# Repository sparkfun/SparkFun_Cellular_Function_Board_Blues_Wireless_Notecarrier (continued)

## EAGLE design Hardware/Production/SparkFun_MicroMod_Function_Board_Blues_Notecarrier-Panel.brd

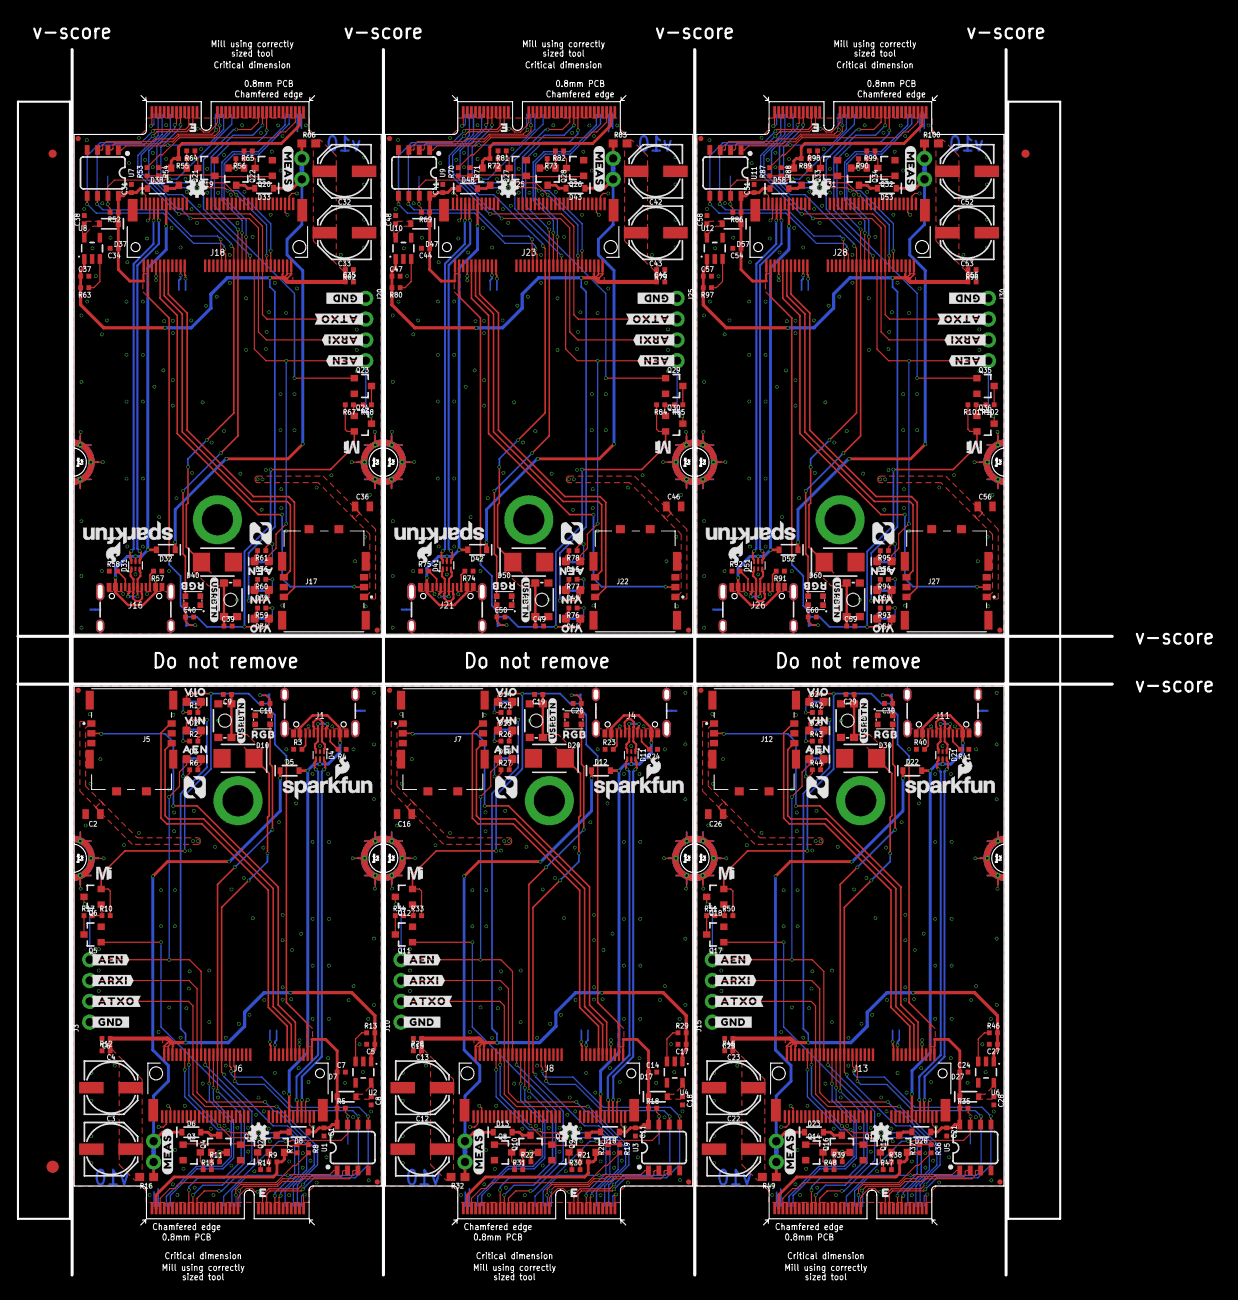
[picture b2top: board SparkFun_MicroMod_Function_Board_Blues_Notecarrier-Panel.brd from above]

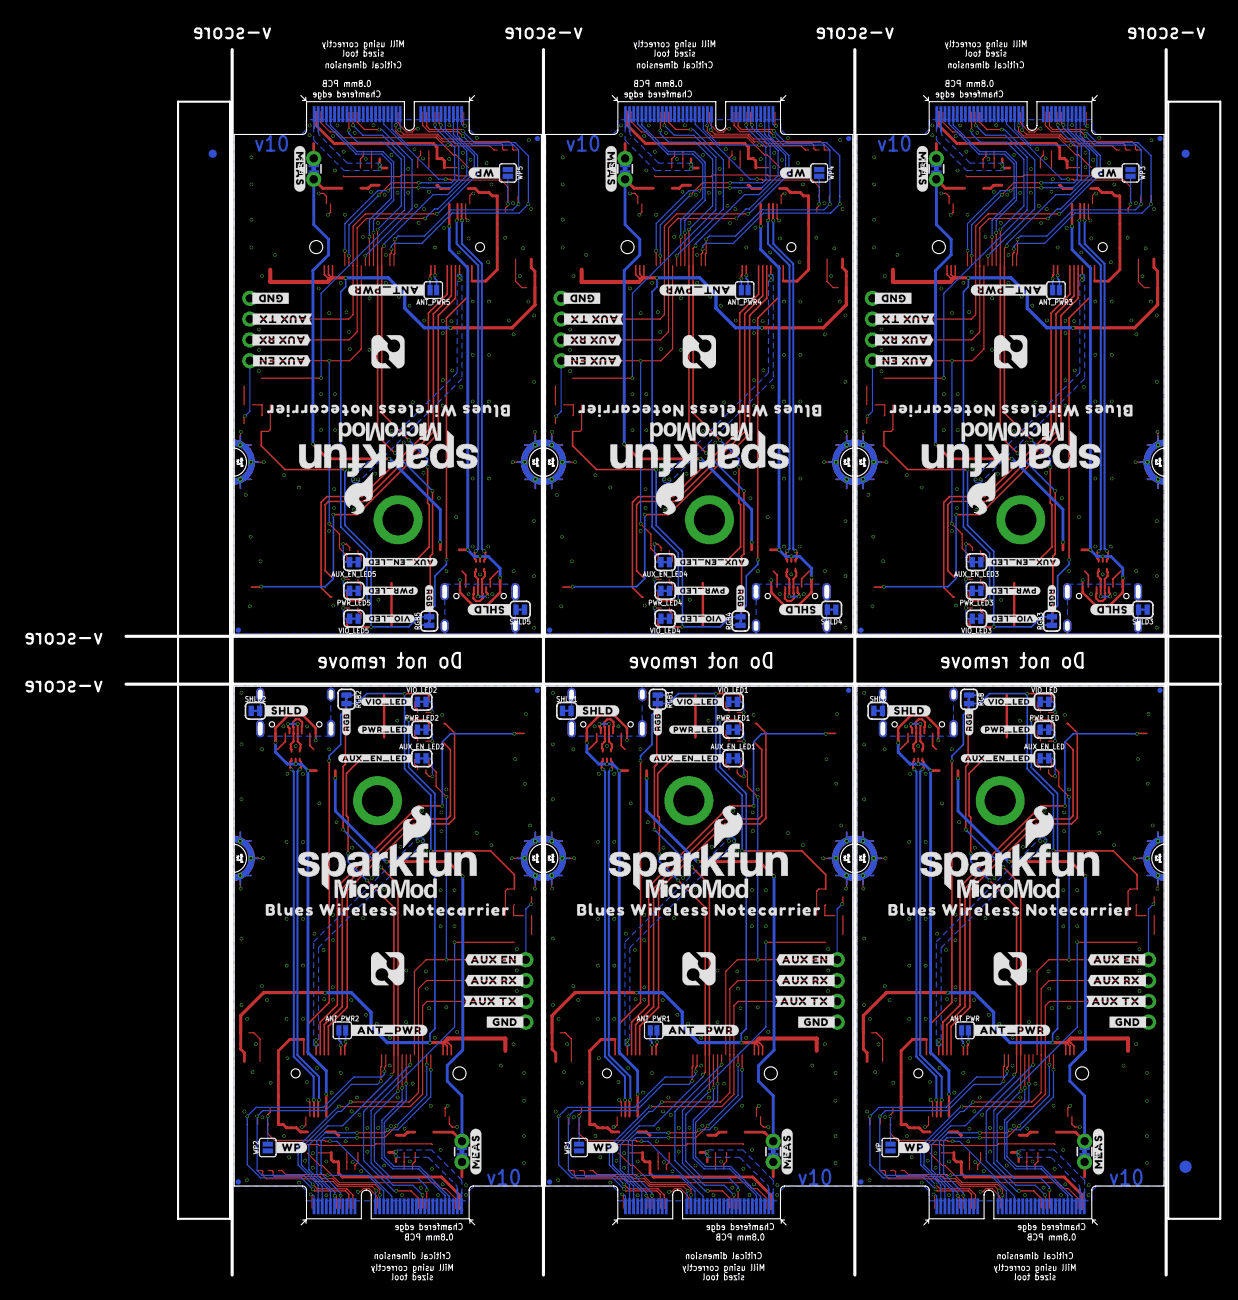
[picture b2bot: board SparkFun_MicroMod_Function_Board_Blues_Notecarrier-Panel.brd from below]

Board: 2 copper layers, 133.6 x 149.6 mm, 576 parts (159 on the bottom side), 342 nets.

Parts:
ANT_PWR, ANT_PWR1, ANT_PWR2, ANT_PWR3, ANT_PWR4, ANT_PWR5: JUMPER-SMT_2_NO_SILK; SMT-JUMPER_2_NO_SILK
AUX_EN_LED, AUX_EN_LED1, AUX_EN_LED2, AUX_EN_LED3, AUX_EN_LED4, AUX_EN_LED5: JUMPER-SMT_2_NC_TRACE_SILK; SMT-JUMPER_2_NC_TRACE_SILK
C1, C5, C6, C7, C10, C11, C14, C15, C17, C20, C21, C24, C25, C27, C30, C31, C34, C35, C37, C40, C41, C44, C45, C47, C50, C51, C54, C55, C57, C60: 0.1uF; 0402-TIGHT
C2, C16, C26, C36, C46, C56: 10uF; 0805
C3, C4, C12, C13, C22, C23, C32, C33, C42, C43, C52, C53: 100uF; PANASONIC_D
C8, C9, C18, C19, C28, C29, C38, C39, C48, C49, C58, C59: 1.0uF; 0402-TIGHT
D1, D2, D14, D15, D24, D25, D34, D35, D44, D45, D54, D55: RED; LED-0603
D3, D16, D26, D36, D46, D56: BLUE; LED-0603
D4, D11, D21, D31, D41, D51: PRTR5V0U2F; SOT886
D5, D6, D12, D13, D22, D23, D32, D33, D42, D43, D52, D53: 3A/10V/280mV; SOD-323
D7, D8, D17, D18, D27, D28, D37, D38, D47, D48, D57, D58: 0.5A/40V/420mV; SOD-323
D9, D19, D29, D39, D49, D59: SMBJP6KE6.8A-TP; DO-214AA
D10, D20, D30, D40, D50, D60: WS2812_2020; WS2812-2020
E$1, E$2, E$3, E$4: FIDUCIAL-1X2
E$5, E$6: FIDUCIAL-1.5X3
FD1, FD2, FD3, FD4, FD5, FD6, FD7, FD8, FD9, FD10, FD11, FD12, FD13, FD14, FD15, FD16, FD17, FD18, FD19, FD20, FD21, FD22, FD23, FD24: FIDUCIALUFIDUCIAL; FIDUCIAL-MICRO
H1, H2, H3, H4, H5, H6: STAND-OFF-REFLOW-M2.5_2.5MM_TALL; STAND-OFF-REFLOW-M2.5
J1, J4, J11, J16, J21, J26: USB-C-16P-2LAYER-PADS
J2, J9, J14, J19, J24, J29: MICROMOD_FUNCTION_STANDARD; M.2-CARD-E-22_FUNCTION_STANDARD
J3, J10, J15, J20, J25, J30: 1X04_NO_SILK
J5, J7, J12, J17, J22, J27: NANO_SIM_MOLEX_104224-0820
J6, J8, J13, J18, J23, J28: NOTECARD; M.2-CONNECTOR-E
LOGO1, LOGO4, LOGO6, LOGO8, LOGO10, LOGO12: SFE_LOGO_NAME_FLAME.1_INCH; SFE_LOGO_NAME_FLAME_.1
LOGO2, LOGO3, LOGO5, LOGO7, LOGO9, LOGO11: OSHW-LOGOMINI; OSHW-LOGO-MINI
MEAS, MEAS1, MEAS2, MEAS3, MEAS4, MEAS5: JUMPER-COMBO_2_NC_TRACE; COMBO-JUMPER_2_NC_TRACE
PWR_LED, PWR_LED1, PWR_LED2, PWR_LED3, PWR_LED4, PWR_LED5: JUMPER-SMT_2_NC_TRACE_SILK; SMT-JUMPER_2_NC_TRACE_SILK
Q1, Q3, Q5, Q7, Q8, Q11, Q13, Q14, Q17, Q19, Q20, Q23, Q25, Q26, Q29, Q31, Q32, Q35: 220mA/50V/3.5Ω; SOT23-3
Q2, Q4, Q6, Q9, Q10, Q12, Q15, Q16, Q18, Q21, Q22, Q24, Q27, Q28, Q30, Q33, Q34, Q36: 20V/4.2A/52mΩ/1.4W; SOT23-3
R1, R2, R25, R26, R42, R43, R59, R60, R76, R77, R93, R94: 1k; 0402-TIGHT
R3, R4, R23, R24, R40, R41, R57, R58, R74, R75, R91, R92: 5.1k; 0402-TIGHT
R5, R7, R9, R10, R11, R13, R18, R20, R21, R22, R29, R33, R35, R37, R38, R39, R46, R50, R52, R54, R55, R56, R63, R67, R69, R71, R72, R73, R80, R84, R86, R88, R89, R90, R97, R101: 10k; 0402-TIGHT
R6, R27, R44, R61, R78, R95: 2.2k; 0402-TIGHT
R8, R19, R36, R53, R70, R87: 560Ω; 0402-TIGHT
R12, R28, R45, R62, R79, R96: 2.2M; 0402-TIGHT
R14, R15, R17, R30, R31, R34, R47, R48, R51, R64, R65, R68, R81, R82, R85, R98, R99, R102: 100; 0402-TIGHT
R16, R32, R49, R66, R83, R100: 1; 0603
RGB, RGB1, RGB2, RGB3, RGB4, RGB5: JUMPER-SMT_2_NC_TRACE_SILK; SMT-JUMPER_2_NC_TRACE_SILK
S1, S2, S3, S4, S5, S6: MOMENTARY-SWITCH-SPST-SMD-4.6X2.8MM; TACTILE_SWITCH_SMD_4.6X2.8MM
SHLD, SHLD1, SHLD2, SHLD3, SHLD4, SHLD5: JUMPER-SMT_2_NC_TRACE_SILK; SMT-JUMPER_2_NC_TRACE_SILK
U1, U3, U5, U7, U9, U11: EEPROM; SO08
U2, U4, U6, U8, U10, U12: TCR2EF33; SOT23-5
U$1, U$27, U$59, U$88, U$117, U$146: AEN1
U$2, U$28, U$60, U$89, U$118, U$147: VIN3
U$3, U$32, U$61, U$90, U$119, U$148: VIO4
U$4, U$42, U$71, U$100, U$129, U$158: #VIO_LED_#21
U$5, U$53, U$82, U$111, U$140, U$169: #_ARXI#0
U$6, U$33, U$62, U$91, U$120, U$149: SFE_LOGO_FLAME_STOP_.1
U$7, U$34, U$63, U$92, U$121, U$150: #_GND_#0
U$8, U$36, U$65, U$94, U$123, U$152: #_WP#2
U$9, U$49, U$78, U$107, U$136, U$165: BLUES_WIRELESS_NOTECARRIER0
U$10, U$50, U$79, U$108, U$137, U$166: NOTEHUB_BLUES#SVG7
U$11, U$54, U$83, U$112, U$141, U$170: #_ATXO#0
U$12, U$51, U$80, U$109, U$138, U$167: #AUX_TX_#0
U$13, U$55, U$84, U$113, U$142, U$171: #_AEN#0
U$14, U$35, U$64, U$93, U$122, U$151: SFE_LOGO_NAME_FLAME_.2
U$15, U$52, U$81, U$110, U$139, U$168: #AUX_RX_#0
U$16, U$17, U$37, U$38, U$66, U$67, U$95, U$96, U$124, U$125, U$153, U$154: #MEAS#4
U$18, U$39, U$68, U$97, U$126, U$155: #_ANT_PWR#5
U$19, U$41, U$70, U$99, U$128, U$157: #AUX_EN_LED_#20
U$20, U$43, U$72, U$101, U$130, U$159: #_SHLD#23
U$21, U$40, U$69, U$98, U$127, U$156: #PWR_LED_#17
U$22, U$44, U$73, U$102, U$131, U$160: #_GND_#24
U$23, U$47, U$76, U$105, U$134, U$163: NOTEHUB_BLUES#SVG5
U$24, U$56, U$85, U$114, U$143, U$172: #RGB_#0
U$25, U$57, U$86, U$115, U$144, U$173: #USRBTN#0
U$26, U$58, U$87, U$116, U$145, U$174: RGB0
U$29, U$45, U$74, U$103, U$132, U$161: MICROMOD_MI_LOGO_.35
U$30, U$46, U$75, U$104, U$133, U$162: #AUX_EN_#0
U$31, U$48, U$77, U$106, U$135, U$164: MICROMOD_LOGO_.5
VIO_LED, VIO_LED1, VIO_LED2, VIO_LED3, VIO_LED4, VIO_LED5: JUMPER-SMT_2_NC_TRACE_SILK; SMT-JUMPER_2_NC_TRACE_SILK
WP, WP1, WP2, WP3, WP4, WP5: JUMPER-SMT_2_NO_SILK; SMT-JUMPER_2_NO_SILK

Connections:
3.3V: C1.1, C7.1, D1.A, D7.C, D8.C, J6.2, J6.4, Q6.2, R5.1, R10.2, RGB.2, U1.8
3.3V1: C11.1, C14.1, D14.A, D17.C, D18.C, J8.2, J8.4, Q12.2, R18.1, R33.2, RGB1.2, U3.8
3.3V2: C21.1, C24.1, D24.A, D27.C, D28.C, J13.2, J13.4, Q18.2, R35.1, R50.2, RGB2.2, U5.8
3.3V3: C31.1, C34.1, D34.A, D37.C, D38.C, J18.2, J18.4, Q24.2, R52.1, R67.2, RGB3.2, U7.8
3.3V4: C41.1, C44.1, D44.A, D47.C, D48.C, J23.2, J23.4, Q30.2, R69.1, R84.2, RGB4.2, U9.8
3.3V5: C51.1, C54.1, D54.A, D57.C, D58.C, J28.2, J28.4, Q36.2, R86.1, R101.2, RGB5.2, U11.8
3V3_IN: J2.73, Q2.2, R7.1, R9.2
3V3_IN1: J9.73, Q9.2, R20.1, R21.2
3V3_IN2: J14.73, Q15.2, R37.1, R38.2
3V3_IN3: J19.73, Q21.2, R54.1, R55.2
3V3_IN4: J24.73, Q27.2, R71.1, R72.2
3V3_IN5: J29.73, Q33.2, R88.1, R89.2
A0: J2.36, U1.1
A1: J2.34, U1.2
A2: J2.32, U1.3
A3: J9.36, U3.1
A4: J9.32, U3.3
A5: J9.34, U3.2
A6: J14.36, U5.1
A7: J14.32, U5.3
A8: J14.34, U5.2
A9: J19.36, U7.1
A10: J19.32, U7.3
A11: J19.34, U7.2
A12: J24.36, U9.1
A13: J24.32, U9.3
A14: J24.34, U9.2
A15: J29.36, U11.1
A16: J29.32, U11.3
A17: J29.34, U11.2
ATTN: J2.53, J6.54
ATTN1: J8.54, J9.53
ATTN2: J13.54, J14.53
ATTN3: J18.54, J19.53
ATTN4: J23.54, J24.53
ATTN5: J28.54, J29.53
AUX1/DFU_!ACTIVE!/USR_BTN: C9.1, D9.C, J2.10, J6.46, S1.3, S1.4
AUX1/DFU_!ACTIVE!/USR_BTN1: C19.1, D19.C, J8.46, J9.10, S2.3, S2.4
AUX1/DFU_!ACTIVE!/USR_BTN2: C29.1, D29.C, J13.46, J14.10, S3.3, S3.4
AUX1/DFU_!ACTIVE!/USR_BTN3: C39.1, D39.C, J18.46, J19.10, S4.3, S4.4
AUX1/DFU_!ACTIVE!/USR_BTN4: C49.1, D49.C, J23.46, J24.10, S5.3, S5.4
AUX1/DFU_!ACTIVE!/USR_BTN5: C59.1, D59.C, J28.46, J29.10, S6.3, S6.4
AUX2/RGB: D10.DI, J2.57, J6.48
AUX2/RGB1: D20.DI, J8.48, J9.57
AUX2/RGB2: D30.DI, J13.48, J14.57
AUX2/RGB3: D40.DI, J18.48, J19.57
AUX2/RGB4: D50.DI, J23.48, J24.57
AUX2/RGB5: D60.DI, J28.48, J29.57
AUX3/DFU_!BOOT!: J2.66, J6.50
AUX3/DFU_!BOOT!1: J8.50, J9.66
AUX3/DFU_!BOOT!2: J13.50, J14.66
AUX3/DFU_!BOOT!3: J18.50, J19.66
AUX3/DFU_!BOOT!4: J23.50, J24.66
AUX3/DFU_!BOOT!5: J28.50, J29.66
AUX4/DFU_!RST!: J2.68, J6.52
AUX4/DFU_!RST!1: J8.52, J9.68
AUX4/DFU_!RST!2: J13.52, J14.68
AUX4/DFU_!RST!3: J18.52, J19.68
AUX4/DFU_!RST!4: J23.52, J24.68
AUX4/DFU_!RST!5: J28.52, J29.68
AUX_EN: D3.A, J3.4, J6.56, Q6.3
AUX_EN1: D16.A, J8.56, J10.4, Q12.3
AUX_EN2: D26.A, J13.56, J15.4, Q18.3
AUX_EN3: D36.A, J18.56, J20.4, Q24.3
AUX_EN4: D46.A, J23.56, J25.4, Q30.3
AUX_EN5: D56.A, J28.56, J30.4, Q36.3
AUX_PWR: J2.55, Q5.1
AUX_PWR1: J9.55, Q11.1
AUX_PWR2: J14.55, Q17.1
AUX_PWR3: J19.55, Q23.1
AUX_PWR4: J24.55, Q29.1
AUX_PWR5: J29.55, Q35.1
AUX_RX/MCU_TX: J2.6, J3.3, J6.58
AUX_RX/MCU_TX1: J8.58, J9.6, J10.3
AUX_RX/MCU_TX2: J13.58, J14.6, J15.3
AUX_RX/MCU_TX3: J18.58, J19.6, J20.3
AUX_RX/MCU_TX4: J23.58, J24.6, J25.3
AUX_RX/MCU_TX5: J28.58, J29.6, J30.3
AUX_TX/MCU_RX: J2.4, J3.2, J6.60
AUX_TX/MCU_RX1: J8.60, J9.4, J10.2
AUX_TX/MCU_RX2: J13.60, J14.4, J15.2
AUX_TX/MCU_RX3: J18.60, J19.4, J20.2
AUX_TX/MCU_RX4: J23.60, J24.4, J25.2
AUX_TX/MCU_RX5: J28.60, J29.4, J30.2
EWP: J2.40, R5.2, U1.7, WP.2
EWP1: J9.40, R18.2, U3.7, WP1.2
EWP2: J14.40, R35.2, U5.7, WP2.2
EWP3: J19.40, R52.2, U7.7, WP3.2
EWP4: J24.40, R69.2, U9.7, WP4.2
EWP5: J29.40, R86.2, U11.7, WP5.2
GND: AUX_EN_LED.1, C1.2, C2.2, C3.-, C4.-, C5.2, C6.2, C7.2, C8.2, C9.2, C10.2, D4.2, D9.A, D10.GND, H1.1, J1.GND, J1.GND2, J2.1, J2.2, J2.8, J2.33, J2.39, J2.45, J2.75, J2.GND1, J2.GND2, J2.GND3, J2.GND4, J2.GND5, J2.GND6, J3.1, J5.G1, J5.G2, J5.G3, J5.G4, J5.S4, J6.3, J6.5, J6.6, J6.11, J6.18, J6.33, J6.39, J6.45, J6.51, J6.57, J6.71, J6.73, PWR_LED.1, Q1.2, Q3.2, Q5.2, R3.1, R4.1, R12.1, S1.1, S1.2, SHLD.1, U1.4, U2.2, VIO_LED.1, WP.1
GND1: AUX_EN_LED1.1, C11.2, C12.-, C13.-, C14.2, C15.2, C16.2, C17.2, C18.2, C19.2, C20.2, D11.2, D19.A, D20.GND, H2.1, J4.GND, J4.GND2, J7.G1, J7.G2, J7.G3, J7.G4, J7.S4, J8.3, J8.5, J8.6, J8.11, J8.18, J8.33, J8.39, J8.45, J8.51, J8.57, J8.71, J8.73, J9.1, J9.2, J9.8, J9.33, J9.39, J9.45, J9.75, J9.GND1, J9.GND2, J9.GND3, J9.GND4, J9.GND5, J9.GND6, J10.1, PWR_LED1.1, Q7.2, Q8.2, Q11.2, R23.1, R24.1, R28.1, S2.1, S2.2, SHLD1.1, U3.4, U4.2, VIO_LED1.1, WP1.1
GND2: AUX_EN_LED2.1, C21.2, C22.-, C23.-, C24.2, C25.2, C26.2, C27.2, C28.2, C29.2, C30.2, D21.2, D29.A, D30.GND, H3.1, J11.GND, J11.GND2, J12.G1, J12.G2, J12.G3, J12.G4, J12.S4, J13.3, J13.5, J13.6, J13.11, J13.18, J13.33, J13.39, J13.45, J13.51, J13.57, J13.71, J13.73, J14.1, J14.2, J14.8, J14.33, J14.39, J14.45, J14.75, J14.GND1, J14.GND2, J14.GND3, J14.GND4, J14.GND5, J14.GND6, J15.1, PWR_LED2.1, Q13.2, Q14.2, Q17.2, R40.1, R41.1, R45.1, S3.1, S3.2, SHLD2.1, U5.4, U6.2, VIO_LED2.1, WP2.1
GND3: AUX_EN_LED3.1, C31.2, C32.-, C33.-, C34.2, C35.2, C36.2, C37.2, C38.2, C39.2, C40.2, D31.2, D39.A, D40.GND, H4.1, J16.GND, J16.GND2, J17.G1, J17.G2, J17.G3, J17.G4, J17.S4, J18.3, J18.5, J18.6, J18.11, J18.18, J18.33, J18.39, J18.45, J18.51, J18.57, J18.71, J18.73, J19.1, J19.2, J19.8, J19.33, J19.39, J19.45, J19.75, J19.GND1, J19.GND2, J19.GND3, J19.GND4, J19.GND5, J19.GND6, J20.1, PWR_LED3.1, Q19.2, Q20.2, Q23.2, R57.1, R58.1, R62.1, S4.1, S4.2, SHLD3.1, U7.4, U8.2, VIO_LED3.1, WP3.1
GND4: AUX_EN_LED4.1, C41.2, C42.-, C43.-, C44.2, C45.2, C46.2, C47.2, C48.2, C49.2, C50.2, D41.2, D49.A, D50.GND, H5.1, J21.GND, J21.GND2, J22.G1, J22.G2, J22.G3, J22.G4, J22.S4, J23.3, J23.5, J23.6, J23.11, J23.18, J23.33, J23.39, J23.45, J23.51, J23.57, J23.71, J23.73, J24.1, J24.2, J24.8, J24.33, J24.39, J24.45, J24.75, J24.GND1, J24.GND2, J24.GND3, J24.GND4, J24.GND5, J24.GND6, J25.1, PWR_LED4.1, Q25.2, Q26.2, Q29.2, R74.1, R75.1, R79.1, S5.1, S5.2, SHLD4.1, U9.4, U10.2, VIO_LED4.1, WP4.1
GND5: AUX_EN_LED5.1, C51.2, C52.-, C53.-, C54.2, C55.2, C56.2, C57.2, C58.2, C59.2, C60.2, D51.2, D59.A, D60.GND, H6.1, J26.GND, J26.GND2, J27.G1, J27.G2, J27.G3, J27.G4, J27.S4, J28.3, J28.5, J28.6, J28.11, J28.18, J28.33, J28.39, J28.45, J28.51, J28.57, J28.71, J28.73, J29.1, J29.2, J29.8, J29.33, J29.39, J29.45, J29.75, J29.GND1, J29.GND2, J29.GND3, J29.GND4, J29.GND5, J29.GND6, J30.1, PWR_LED5.1, Q31.2, Q32.2, Q35.2, R91.1, R92.1, R96.1, S6.1, S6.2, SHLD5.1, U11.4, U12.2, VIO_LED5.1, WP5.1
unnamed: J2.71, R8.2
unnamed: Q2.1, R9.1, R14.2
unnamed: Q4.1, R11.1, R15.2
unnamed: D1.C, R1.2
unnamed: R13.1, U2.3
unnamed: D2.C, R2.2
unnamed: D8.A, Q2.3
unnamed: J1.B5, R3.2
unnamed: J1.A5, R4.2
unnamed: C8.1, D7.A, U2.5
unnamed: PWR_LED.2, R2.1
unnamed: R1.1, VIO_LED.2
unnamed: D3.C, R6.2
unnamed: AUX_EN_LED.2, R6.1
unnamed: Q1.3, R14.1
unnamed: Q3.3, R15.1
unnamed: MEAS.2, MEAS.4, R16.1
unnamed: C10.1, D10.VCC, RGB.1
unnamed: Q6.1, R10.1, R17.2
unnamed: Q5.3, R17.1
unnamed: J9.71, R19.2
unnamed: Q9.1, R21.1, R30.2
unnamed: Q10.1, R22.1, R31.2
unnamed: J4.B5, R23.2
unnamed: J4.A5, R24.2
unnamed: D12.C, D13.C, MEAS1.1, MEAS1.3
unnamed: D14.C, R25.2
unnamed: D15.C, R26.2
unnamed: PWR_LED1.2, R26.1
unnamed: R25.1, VIO_LED1.2
unnamed: D16.C, R27.2
unnamed: AUX_EN_LED1.2, R27.1
unnamed: R29.1, U4.3
unnamed: C18.1, D17.A, U4.5
unnamed: D18.A, Q9.3
unnamed: Q7.3, R30.1
unnamed: D5.C, D6.C, MEAS.1, MEAS.3
unnamed: Q8.3, R31.1
unnamed: MEAS1.2, MEAS1.4, R32.1
unnamed: C20.1, D20.VCC, RGB1.1
unnamed: Q12.1, R33.1, R34.2
unnamed: Q11.3, R34.1
unnamed: J14.71, R36.2
unnamed: Q15.1, R38.1, R47.2
unnamed: Q16.1, R39.1, R48.2
unnamed: J11.B5, R40.2
unnamed: J11.A5, R41.2
unnamed: D22.C, D23.C, MEAS2.1, MEAS2.3
unnamed: D24.C, R42.2
unnamed: D25.C, R43.2
unnamed: PWR_LED2.2, R43.1
unnamed: R42.1, VIO_LED2.2
unnamed: D26.C, R44.2
unnamed: AUX_EN_LED2.2, R44.1
unnamed: R46.1, U6.3
unnamed: C28.1, D27.A, U6.5
unnamed: D28.A, Q15.3
unnamed: Q13.3, R47.1
unnamed: Q14.3, R48.1
unnamed: MEAS2.2, MEAS2.4, R49.1
unnamed: C30.1, D30.VCC, RGB2.1
unnamed: Q18.1, R50.1, R51.2
unnamed: Q17.3, R51.1
unnamed: J19.71, R53.2
unnamed: Q21.1, R55.1, R64.2
unnamed: Q22.1, R56.1, R65.2
unnamed: J16.B5, R57.2
unnamed: J16.A5, R58.2
unnamed: D32.C, D33.C, MEAS3.1, MEAS3.3
unnamed: D34.C, R59.2
unnamed: D35.C, R60.2
unnamed: PWR_LED3.2, R60.1
unnamed: R59.1, VIO_LED3.2
unnamed: D36.C, R61.2
unnamed: AUX_EN_LED3.2, R61.1
unnamed: R63.1, U8.3
unnamed: C38.1, D37.A, U8.5
unnamed: D38.A, Q21.3
unnamed: Q19.3, R64.1
unnamed: Q20.3, R65.1
unnamed: MEAS3.2, MEAS3.4, R66.1
unnamed: C40.1, D40.VCC, RGB3.1
unnamed: Q24.1, R67.1, R68.2
unnamed: Q23.3, R68.1
unnamed: J24.71, R70.2
unnamed: Q27.1, R72.1, R81.2
unnamed: Q28.1, R73.1, R82.2
unnamed: J21.B5, R74.2
unnamed: J21.A5, R75.2
unnamed: D42.C, D43.C, MEAS4.1, MEAS4.3
unnamed: D44.C, R76.2
unnamed: D45.C, R77.2
unnamed: PWR_LED4.2, R77.1
unnamed: R76.1, VIO_LED4.2
unnamed: D46.C, R78.2
unnamed: AUX_EN_LED4.2, R78.1
unnamed: R80.1, U10.3
unnamed: C48.1, D47.A, U10.5
unnamed: D48.A, Q27.3
unnamed: Q25.3, R81.1
unnamed: Q26.3, R82.1
unnamed: MEAS4.2, MEAS4.4, R83.1
unnamed: C50.1, D50.VCC, RGB4.1
unnamed: Q30.1, R84.1, R85.2
unnamed: Q29.3, R85.1
unnamed: J29.71, R87.2
unnamed: Q33.1, R89.1, R98.2
unnamed: Q34.1, R90.1, R99.2
unnamed: J26.B5, R91.2
unnamed: J26.A5, R92.2
unnamed: D52.C, D53.C, MEAS5.1, MEAS5.3
unnamed: D54.C, R93.2
unnamed: D55.C, R94.2
unnamed: PWR_LED5.2, R94.1
unnamed: R93.1, VIO_LED5.2
unnamed: D56.C, R95.2
unnamed: AUX_EN_LED5.2, R95.1
unnamed: R97.1, U12.3
unnamed: C58.1, D57.A, U12.5
unnamed: D58.A, Q33.3
unnamed: Q31.3, R98.1
unnamed: Q32.3, R99.1
unnamed: MEAS5.2, MEAS5.4, R100.1
unnamed: C60.1, D60.VCC, RGB5.1
unnamed: Q36.1, R101.1, R102.2
unnamed: Q35.3, R102.1
NOTECARD_RX: J2.15, J6.62
NOTECARD_RX1: J8.62, J9.15
NOTECARD_RX2: J13.62, J14.15
NOTECARD_RX3: J18.62, J19.15
NOTECARD_RX4: J23.62, J24.15
NOTECARD_RX5: J28.62, J29.15
NOTECARD_TX: J2.13, J6.64
NOTECARD_TX1: J8.64, J9.13
NOTECARD_TX2: J13.64, J14.13
NOTECARD_TX3: J18.64, J19.13
NOTECARD_TX4: J23.64, J24.13
NOTECARD_TX5: J28.64, J29.13
PWR_EN: Q1.1, Q3.1, R7.2, R8.1
PWR_EN1: Q7.1, Q8.1, R19.1, R20.2
PWR_EN2: Q13.1, Q14.1, R36.1, R37.2
PWR_EN3: Q19.1, Q20.1, R53.1, R54.2
PWR_EN4: Q25.1, Q26.1, R70.1, R71.2
PWR_EN5: Q31.1, Q32.1, R87.1, R88.2
SCL: J2.21, J6.40, U1.6
SCL1: J8.40, J9.21, U3.6
SCL2: J13.40, J14.21, U5.6
SCL3: J18.40, J19.21, U7.6
SCL4: J23.40, J24.21, U9.6
SCL5: J28.40, J29.21, U11.6
SDA: J2.19, J6.42, U1.5
SDA1: J8.42, J9.19, U3.5
SDA2: J13.42, J14.19, U5.5
SDA3: J18.42, J19.19, U7.5
SDA4: J23.42, J24.19, U9.5
SDA5: J28.42, J29.19, U11.5
SHLD: J1.SHLD1, J1.SHLD2, J1.SHLD3, J1.SHLD4, SHLD.2
SHLD1: J4.SHLD1, J4.SHLD2, J4.SHLD3, J4.SHLD4, SHLD1.2
SHLD2: J11.SHLD1, J11.SHLD2, J11.SHLD3, J11.SHLD4, SHLD2.2
SHLD3: J16.SHLD1, J16.SHLD2, J16.SHLD3, J16.SHLD4, SHLD3.2
SHLD4: J21.SHLD1, J21.SHLD2, J21.SHLD3, J21.SHLD4, SHLD4.2
SHLD5: J26.SHLD1, J26.SHLD2, J26.SHLD3, J26.SHLD4, SHLD5.2
SIM_CLK: J5.S3, J6.14
SIM_CLK1: J7.S3, J8.14
SIM_CLK2: J12.S3, J13.14
SIM_CLK3: J17.S3, J18.14
SIM_CLK4: J22.S3, J23.14
SIM_CLK5: J27.S3, J28.14
SIM_IO: J5.S6, J6.12
SIM_IO1: J7.S6, J8.12
SIM_IO2: J12.S6, J13.12
SIM_IO3: J17.S6, J18.12
SIM_IO4: J22.S6, J23.12
SIM_IO5: J27.S6, J28.12
SIM_RST: J5.S2, J6.10
SIM_RST1: J7.S2, J8.10
SIM_RST2: J12.S2, J13.10
SIM_RST3: J17.S2, J18.10
SIM_RST4: J22.S2, J23.10
SIM_RST5: J27.S2, J28.10
SIM_VCC: C2.1, J5.S1, J6.8
SIM_VCC1: C16.1, J7.S1, J8.8
SIM_VCC2: C26.1, J12.S1, J13.8
SIM_VCC3: C36.1, J17.S1, J18.8
SIM_VCC4: C46.1, J22.S1, J23.8
SIM_VCC5: C56.1, J27.S1, J28.8
USB_IN_N: D4.3, J1.A7, J1.B7
USB_IN_N1: D11.3, J4.A7, J4.B7
USB_IN_N2: D21.3, J11.A7, J11.B7
USB_IN_N3: D31.3, J16.A7, J16.B7
USB_IN_N4: D41.3, J21.A7, J21.B7
USB_IN_N5: D51.3, J26.A7, J26.B7
USB_IN_P: D4.1, J1.A6, J1.B6
USB_IN_P1: D11.1, J4.A6, J4.B6
USB_IN_P2: D21.1, J11.A6, J11.B6
USB_IN_P3: D31.1, J16.A6, J16.B6
USB_IN_P4: D41.1, J21.A6, J21.B6
USB_IN_P5: D51.1, J26.A6, J26.B6
USB_N: D4.4, J6.9
USB_N1: D11.4, J8.9
USB_N2: D21.4, J13.9
USB_N3: D31.4, J18.9
USB_N4: D41.4, J23.9
USB_N5: D51.4, J28.9
USB_P: D4.6, J6.7
USB_P1: D11.6, J8.7
USB_P2: D21.6, J13.7
USB_P3: D31.6, J18.7
USB_P4: D41.6, J23.7
USB_P5: D51.6, J28.7
VACT_GPS_IN: ANT_PWR.2, J6.22
VACT_GPS_IN1: ANT_PWR1.2, J8.22
VACT_GPS_IN2: ANT_PWR2.2, J13.22
VACT_GPS_IN3: ANT_PWR3.2, J18.22
VACT_GPS_IN4: ANT_PWR4.2, J23.22
VACT_GPS_IN5: ANT_PWR5.2, J28.22
VACT_GPS_OUT: ANT_PWR.1, J6.20
VACT_GPS_OUT1: ANT_PWR1.1, J8.20
VACT_GPS_OUT2: ANT_PWR2.1, J13.20
VACT_GPS_OUT3: ANT_PWR3.1, J18.20
VACT_GPS_OUT4: ANT_PWR4.1, J23.20
VACT_GPS_OUT5: ANT_PWR5.1, J28.20
VCC: D6.A, Q4.3
VCC1: D13.A, Q10.3
VCC2: D23.A, Q16.3
VCC3: D33.A, Q22.3
VCC4: D43.A, Q28.3
VCC5: D53.A, Q34.3
VCC_IN: J2.72, J2.74, Q4.2, R11.2
VCC_IN1: J9.72, J9.74, Q10.2, R22.2
VCC_IN2: J14.72, J14.74, Q16.2, R39.2
VCC_IN3: J19.72, J19.74, Q22.2, R56.2
VCC_IN4: J24.72, J24.74, Q28.2, R73.2
VCC_IN5: J29.72, J29.74, Q34.2, R90.2
VIN: C3.+, C4.+, C5.1, C6.1, D2.A, J6.70, J6.72, J6.74, R12.2, R13.2, R16.2, U2.1
VIN1: C12.+, C13.+, C15.1, C17.1, D15.A, J8.70, J8.72, J8.74, R28.2, R29.2, R32.2, U4.1
VIN2: C22.+, C23.+, C25.1, C27.1, D25.A, J13.70, J13.72, J13.74, R45.2, R46.2, R49.2, U6.1
VIN3: C32.+, C33.+, C35.1, C37.1, D35.A, J18.70, J18.72, J18.74, R62.2, R63.2, R66.2, U8.1
VIN4: C42.+, C43.+, C45.1, C47.1, D45.A, J23.70, J23.72, J23.74, R79.2, R80.2, R83.2, U10.1
VIN5: C52.+, C53.+, C55.1, C57.1, D55.A, J28.70, J28.72, J28.74, R96.2, R97.2, R100.2, U12.1
V_USB: D4.5, D5.A, J1.VBUS1, J1.VBUS2, J6.13
V_USB1: D11.5, D12.A, J4.VBUS1, J4.VBUS2, J8.13
V_USB2: D21.5, D22.A, J11.VBUS1, J11.VBUS2, J13.13
V_USB3: D31.5, D32.A, J16.VBUS1, J16.VBUS2, J18.13
V_USB4: D41.5, D42.A, J21.VBUS1, J21.VBUS2, J23.13
V_USB5: D51.5, D52.A, J26.VBUS1, J26.VBUS2, J28.13

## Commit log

2022-06-16 Initial Commit.
    Added Notecard part in library. Edited symbol to fit style guidelines.
    Added Notecard and MMFB connectors.
2022-06-23 Board nearly complete, nearing readiness for design review.
2022-06-23 Board routing complete.
    Initial routing complete, now finishing silk.
2022-06-23 Initial Silk completed.
    May add Blues Wireless logo.
2022-06-23 Added measures on board.
2022-06-23 Add production notes on board file.
2022-06-23 Added micromod silks.
2022-06-24 Post DR updates.
    Schematic:
    Add Text to VREG
    Add Text to Notecard
    add 100 ohm resistor on pwr ctrl
    Change Q1/Q3 transistors
    Add Text to jumpers
2022-06-24 Change one trace for ground pour.
2022-06-24 Add protos production files.
2022-06-27 Update gitignore and readme
    gitignore added images.
    Updated readme file to match decided product name.
2022-06-27 Deleted extra v-score text in panel.
2022-08-16 Add PROD_ID to M.2 Connector for Notecard.
2022-08-18 Update to v02.
    Remove 10k PUR on AUX_EN
    Add P-ch FET switch to AUX_EN
    Rear Silk
    Add Notecard SVG to silk
    Change Title of Reset Section of Schematic
    Reduce value of AEN LED bias resistor
2022-08-18 Change footprint to pass board auto checklist
2022-08-18 Added v02 panel/gerbers.
2022-08-22 Swap Notecard RX/TX, add missing silk, add diode PROD-ID.
2022-08-24 Rev to v10. Update RGB Silk. Repanelize for changes.
2022-09-02 Rev v11
    AEN wasn't enabled by default because it was missing a passive. Added passive and rerouted.
2022-09-14 Update pin visibility for dbg.
2022-10-21 Updated to replace EOL caps.
2022-11-01 DNP unused diode.
2022-11-02 Added Example01 with data collection.
2022-11-03 Add Example02: Outboard DFU.
2023-01-03 Populated product page link in examples.
2023-01-05 Update README.md
    Updating README.md for product release.
